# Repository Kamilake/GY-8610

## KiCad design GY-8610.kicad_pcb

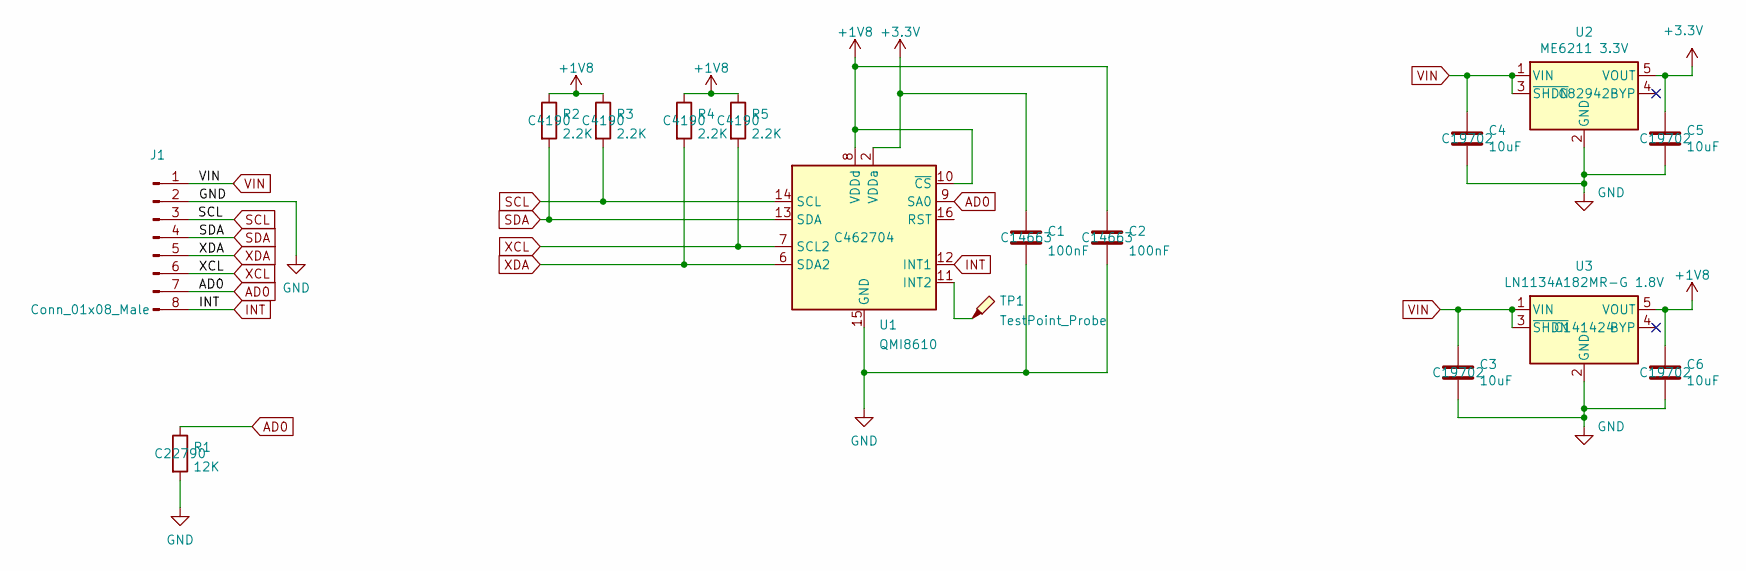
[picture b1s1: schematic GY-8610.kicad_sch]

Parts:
C1, C2: 100nF; C_0603_1608Metric; LCSC C14663
C3, C4, C5, C6: 10uF; C_0603_1608Metric; LCSC C19702
J1: Conn_01x08_Male; PinHeader_1x08_P2.54mm_Vertical
R1: 12K; R_0603_1608Metric; LCSC C22790
R2, R3, R4, R5: 2.2K; R_0603_1608Metric; LCSC C4190
TP1: TestPoint_Probe; TestPoint_Pad_D1.0mm
U1: QMI8610; LGA-16_3x3mm_P0.5mm_LayoutBorder3x5y; LCSC C462704
U2: ME6211 3.3V; SOT-23-5; LCSC C82942
U3: LN1134A182MR-G 1.8V; SOT-23-5; LCSC C141424

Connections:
+1V8: C2.2, C6.1, R2.1, R3.1, R4.1, R5.1, U1.8 (VDDd), U1.10 (~CS), U3.5 (VOUT)
+3V3: C1.2, C5.1, U1.2 (VDDa), U2.5 (VOUT)
AD0: J1.7, R1.1, U1.9 (SA0)
GND: C1.1, C2.1, C3.2, C4.2, C5.2, C6.2, J1.2, R1.2, U1.1 (RESV3), U1.3 (GND), U1.15 (GND), U2.2 (GND), U3.2 (GND)
INT: J1.8, U1.12 (INT1)
unnamed: TP1.1, U1.11 (INT2)
SCL: J1.3, R3.2, U1.14 (SCL)
SDA: J1.4, R2.2, U1.13 (SDA)
VIN: C3.1, C4.1, J1.1, U2.1 (VIN), U2.3 (~SHDN), U3.1 (VIN), U3.3 (~SHDN)
XCL: J1.6, R5.2, U1.7 (SCL2)
XDA: J1.5, R4.2, U1.6 (SDA2)

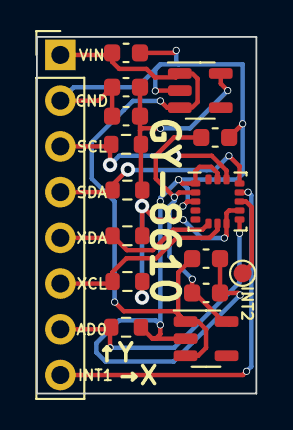
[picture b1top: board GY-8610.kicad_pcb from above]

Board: 2 copper layers, 12.2 x 19.8 mm, 16 parts (0 on the bottom side), 11 nets.

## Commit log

2022-03-22 Kami!
